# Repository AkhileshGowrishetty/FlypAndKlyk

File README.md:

# FlypAndKlyk
Self-sustaining system used to call office staff on demand using nRF24L01 and ATMEGA328P.

# Images
<kbd></kbd><kbd></kbd>

<kbd></kbd><kbd></kbd>

<kbd></kbd><kbd></kbd>

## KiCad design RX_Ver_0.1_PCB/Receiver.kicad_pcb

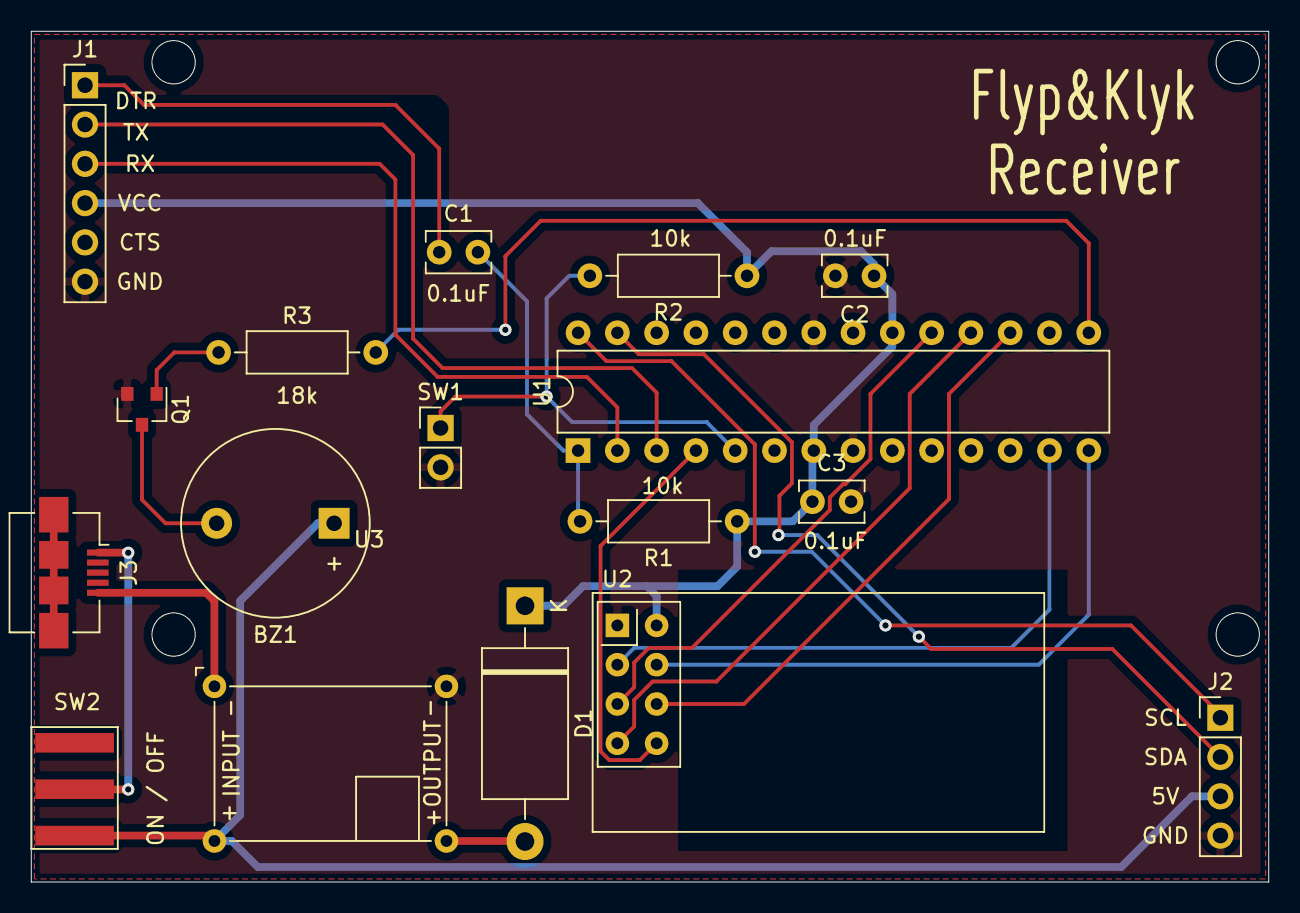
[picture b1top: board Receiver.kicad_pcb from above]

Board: 2 copper layers, 80.0 x 55.0 mm, 17 parts (0 on the bottom side), 22 nets.

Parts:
BZ1: Buzzer; Buzzer_12x9.5RM7.6
C1, C2, C3: 0.1uF; C_Rect_L4.0mm_W2.5mm_P2.50mm
D1: DIODE; D_DO-27_P15.24mm_Horizontal
J1: Conn_01x06; PinHeader_1x06_P2.54mm_Vertical
J2: Conn_01x04; PinHeader_1x04_P2.54mm_Vertical
J3: USB_B_Micro; USB_Micro-B_Amphenol_10104110_Horizontal
Q1: BC847; SOT-23
R1, R2: 10k; R_Axial_DIN0207_L6.3mm_D2.5mm_P10.16mm_Horizontal
R3: 18k; R_Axial_DIN0207_L6.3mm_D2.5mm_P10.16mm_Horizontal
SW1: SW_Push; PinHeader_1x02_P2.54mm_Vertical
SW2: SW_DPDT_x2; Slide_Switch
U1: ATmega328P-PU; DIP-28_W7.62mm
U2: NRF24L01_Breakout; nRF24L01_Breakout
U3: MP1584_BuckConverter_3A; MP1584_3A_Buck

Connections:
+5V: BZ1.1, J2.3, SW2.3, U3.1
BUZZER: R3.2, U1.15
CE: U1.13, U2.3
CSN: U1.14, U2.4
DTR: C1.2, R1.2, U1.1
DTR_FTDI: C1.1, J1.1
GND: C2.2, C3.2, J1.6, J2.4, Q1.2, SW1.2, U1.8, U1.22, U2.1, U3.4
IRQ: U1.4, U2.8
MISO: U1.18, U2.7
MOSI: U1.17, U2.6
unnamed: BZ1.2, Q1.3
unnamed: D1.2, U3.3
unnamed: J3.1, SW2.2
unnamed: J3.5, U3.2
unnamed: Q1.1, R3.1
unnamed: R2.2, SW1.1, U1.5
RX: J1.3, U1.2
SCK: U1.19, U2.5
SCL: J2.1, U1.28
SDA: J2.2, U1.27
TX: J1.2, U1.3
VCC: C2.1, C3.1, D1.1, J1.4, R1.1, R2.1, U1.7, U1.20, U2.2

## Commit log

2021-04-08 RX PCB Schematics and Design
2021-04-08 3D Cases & TX PCB
2021-04-08 Moved TX 3D Case location
2021-04-20 Update about PCB Design and 3D case
2021-04-20 Rename Note to README.md
2021-04-20 Added Images of Receiver and Transmitter
2021-04-20 Update README.md
    Added Images
